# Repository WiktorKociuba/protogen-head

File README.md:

# Protogen head
**WIP**
## Hardware
The PCB for this protogen head contains ESP32-S3-Mini and is powered by two USB-C ports/one USB-C port and XT-30 connector. You can connect to it:
- Two serialy connected Waveshare 22101 (or simillar) LED matrixes
- Two WS2812B LED strips
- Two small fans
- One speaker
- One capacitive button <br>

It also has 15 GPIO pins exposed as well as two of each voltage pins. The +5VD net is used to power only LED Matrixes and the +5V powers the rest. ESP32 works on 3V3, so I had to use a LDO to power it. There are also two 74AHCT245PW used to change the logic voltage from 3V3 to 5V, so it can communicate with the peripherals that require 5V. The production files and LCSC BoM can be found in hardware/protogenHead/jlcpcb/production_files . <br>
 <br>
<br>
<br>
<br>

## 3D Model
**TODO**
## Software
**TODO**

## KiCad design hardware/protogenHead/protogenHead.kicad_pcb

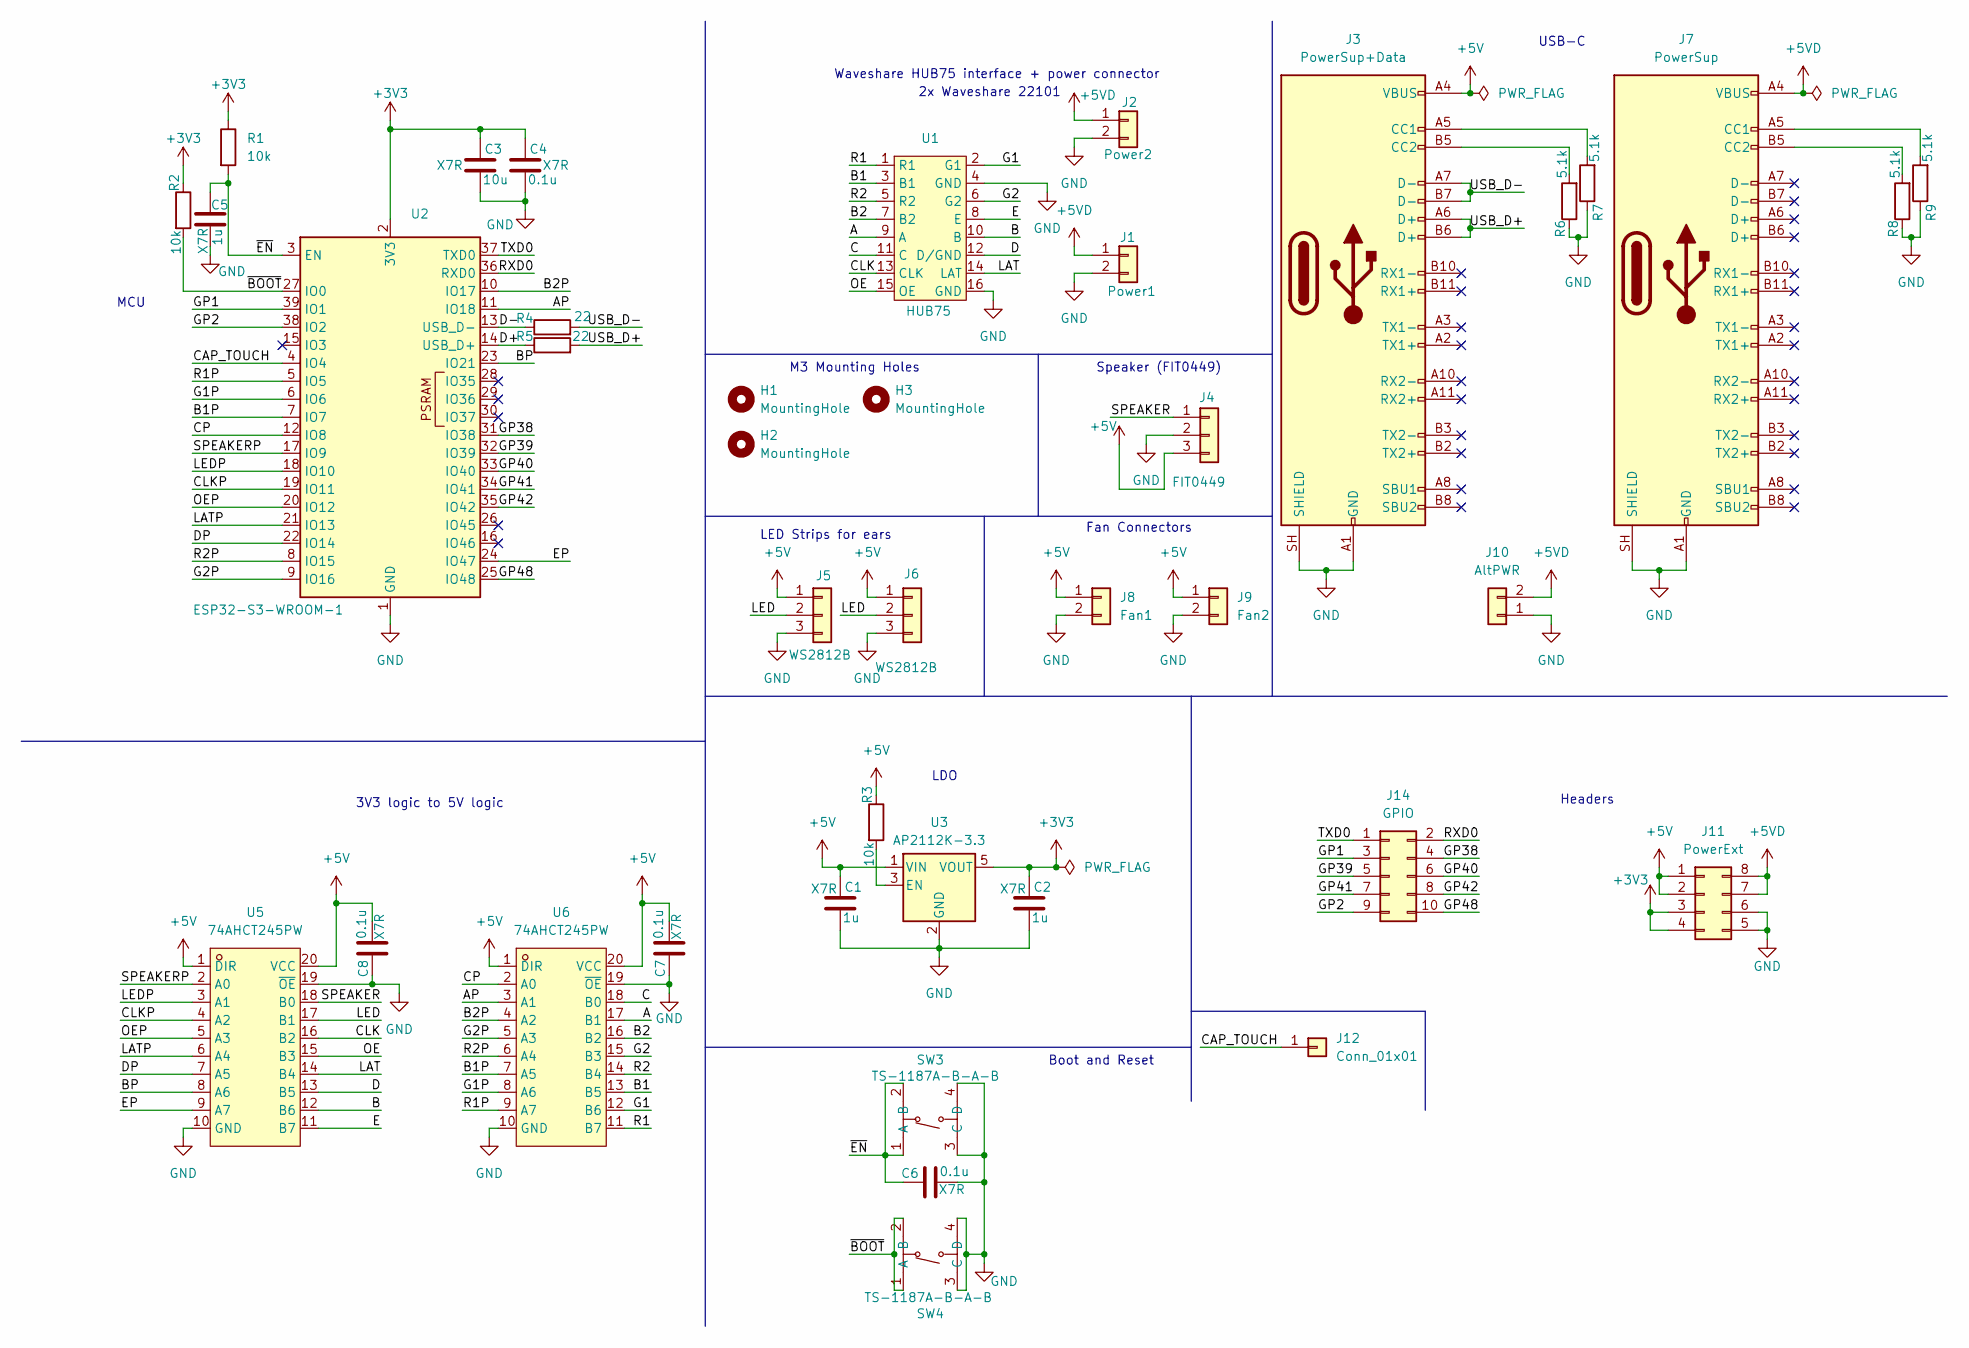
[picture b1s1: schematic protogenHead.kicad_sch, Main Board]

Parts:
C1, C2, C5: 1u; C_0603_1608Metric
C3: 10u; C_0603_1608Metric
C4, C6, C7, C8: 0.1u; C_0603_1608Metric
H1, H2, H3: MountingHole; MountingHole_3.2mm_M3
J1: Power1; TerminalBlock_MaiXu_MX126-5.0-02P_1x02_P5.00mm
J2: Power2; TerminalBlock_MaiXu_MX126-5.0-02P_1x02_P5.00mm
J3: PowerSup+Data; USB_C_Receptacle_HRO_TYPE-C-31-M-12
J4: FIT0449; JST_EH_B3B-EH-A_1x03_P2.50mm_Vertical
J5, J6: WS2812B; JST_EH_B3B-EH-A_1x03_P2.50mm_Vertical
J7: PowerSup; USB_C_Receptacle_HRO_TYPE-C-31-M-12
J8: Fan1; JST_EH_B2B-EH-A_1x02_P2.50mm_Vertical
J9: Fan2; JST_EH_B2B-EH-A_1x02_P2.50mm_Vertical
J10: AltPWR; AMASS_XT30U-F_1x02_P5.0mm_Vertical
J11: PowerExt; PinHeader_2x04_P2.54mm_Vertical
J12: Conn_01x01; PinSocket_1x01_P2.54mm_Vertical
J14: GPIO; PinHeader_2x05_P2.54mm_Vertical
R1, R2, R3: 10k; R_0603_1608Metric
R4, R5: 22; R_0603_1608Metric
R6, R7, R8, R9: 5.1k; R_0603_1608Metric
SW3, SW4: TS-1187A-B-A-B; SW-SMD_4P-L5.1-W5.1-P3.70-LS6.5-TL_H1.5; MPN TS-1187A-B-A-B; LCSC Part C318884
U1: HUB75; IDC-Header_2x08_P2.54mm_Vertical
U2: ESP32-S3-WROOM-1
U3: AP2112K-3.3; SOT-23-5
U5, U6: 74AHCT245PW; TSSOP-20_L6.5-W4.4-P0.65-LS6.4-BL; MPN 74AHCT245PW; LCSC Part C54815895

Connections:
+3V3: C2.1, C3.1, C4.1, J11.3, J11.4, R1.1, R2.1, U2.2 (3V3), U3.5 (VOUT)
+5V: C1.1, C7.2, C8.2, J3.A4 (VBUS), J3.A9 (VBUS), J3.B4 (VBUS), J3.B9 (VBUS), J4.3, J5.1, J6.1, J8.1, J9.1, J11.1, J11.2, R3.1, U3.1 (VIN), U5.1 (DIR), U5.20 (VCC), U6.1 (DIR), U6.20 (VCC)
+5VD: J1.1, J2.1, J7.A4 (VBUS), J7.A9 (VBUS), J7.B4 (VBUS), J7.B9 (VBUS), J10.2, J11.7, J11.8
/A: U1.9 (A), U6.17 (B1)
/AP: U2.11 (IO18), U6.3 (A1)
/B: U1.10 (B), U5.12 (B6)
/B1: U1.3 (B1), U6.13 (B5)
/B1P: U2.7 (IO7), U6.7 (A5)
/B2: U1.7 (B2), U6.16 (B2)
/B2P: U2.10 (IO17), U6.4 (A2)
/BP: U2.23 (IO21), U5.8 (A6)
/C: U1.11 (C), U6.18 (B0)
/CAP_TOUCH: J12.1 (Pin_1_1), U2.4 (IO4)
/CLK: U1.13 (CLK), U5.16 (B2)
/CLKP: U2.19 (IO11), U5.4 (A2)
/CP: U2.12 (IO8), U6.2 (A0)
/D: U1.12 (D/GND), U5.13 (B5)
/D+: R5.1, U2.14 (USB_D+)
/D-: R4.1, U2.13 (USB_D-)
/DP: U2.22 (IO14), U5.7 (A5)
/E: U1.8 (E), U5.11 (B7)
/EP: U2.24 (IO47), U5.9 (A7)
/G1: U1.2 (G1), U6.12 (B6)
/G1P: U2.6 (IO6), U6.8 (A6)
/G2: U1.6 (G2), U6.15 (B3)
/G2P: U2.9 (IO16), U6.5 (A3)
/GP1: J14.3, U2.39 (IO1)
/GP2: J14.9, U2.38 (IO2)
/GP38: J14.4, U2.31 (IO38)
/GP39: J14.5, U2.32 (IO39)
/GP40: J14.6, U2.33 (IO40)
/GP41: J14.7, U2.34 (IO41)
/GP42: J14.8, U2.35 (IO42)
/GP48: J14.10, U2.25 (IO48)
/LAT: U1.14 (LAT), U5.14 (B4)
/LATP: U2.21 (IO13), U5.6 (A4)
/LED: J5.2, J6.2, U5.17 (B1)
/LEDP: U2.18 (IO10), U5.3 (A1)
/OE: U1.15 (OE), U5.15 (B3)
/OEP: U2.20 (IO12), U5.5 (A3)
/R1: U1.1 (R1), U6.11 (B7)
/R1P: U2.5 (IO5), U6.9 (A7)
/R2: U1.5 (R2), U6.14 (B4)
/R2P: U2.8 (IO15), U6.6 (A4)
/RXD0: J14.2, U2.36 (RXD0)
/SPEAKER: J4.1, U5.18 (B0)
/SPEAKERP: U2.17 (IO9), U5.2 (A0)
/TXD0: J14.1, U2.37 (TXD0)
/USB_D+: J3.A6 (D+), J3.B6 (D+), R5.2
/USB_D-: J3.A7 (D-), J3.B7 (D-), R4.2
/~BOOT: R2.2, SW4.1 (A), SW4.2 (B), U2.27 (IO0)
/~EN: C5.1, C6.1, R1.2, SW3.1 (A), SW3.2 (B), U2.3 (EN)
GND: C1.2, C2.2, C3.2, C4.2, C5.2, C6.2, C7.1, C8.1, J1.2, J2.2, J3.A1 (GND), J3.A12 (GND), J3.B1 (GND), J3.B12 (GND), J3.SH (SHIELD), J4.2, J5.3, J6.3, J7.A1 (GND), J7.A12 (GND), J7.B1 (GND), J7.B12 (GND), J7.SH (SHIELD), J8.2, J9.2, J10.1, J11.5, J11.6, R6.1, R7.1, R8.1, R9.1, SW3.3 (C), SW3.4 (D), SW4.3 (C), SW4.4 (D), U1.4 (GND), U1.16 (GND), U2.1 (GND), U2.40 (GND), U2.41 (GND), U3.2 (GND), U5.10 (GND), U5.19 (~OE), U6.10 (GND), U6.19 (~OE)
unnamed: J3.A5 (CC1), R7.2
unnamed: J3.B5 (CC2), R6.2
unnamed: J7.A5 (CC1), R9.2
unnamed: J7.B5 (CC2), R8.2
unnamed: R3.2, U3.3 (EN)

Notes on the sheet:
3V3 logic to 5V logic
Boot and Reset
M3 Mounting Holes
USB-C
Fan Connectors
Speaker (FIT0449)
LDO
Waveshare HUB75 interface + power connector
LED Strips for ears
2x Waveshare 22101
Headers
MCU

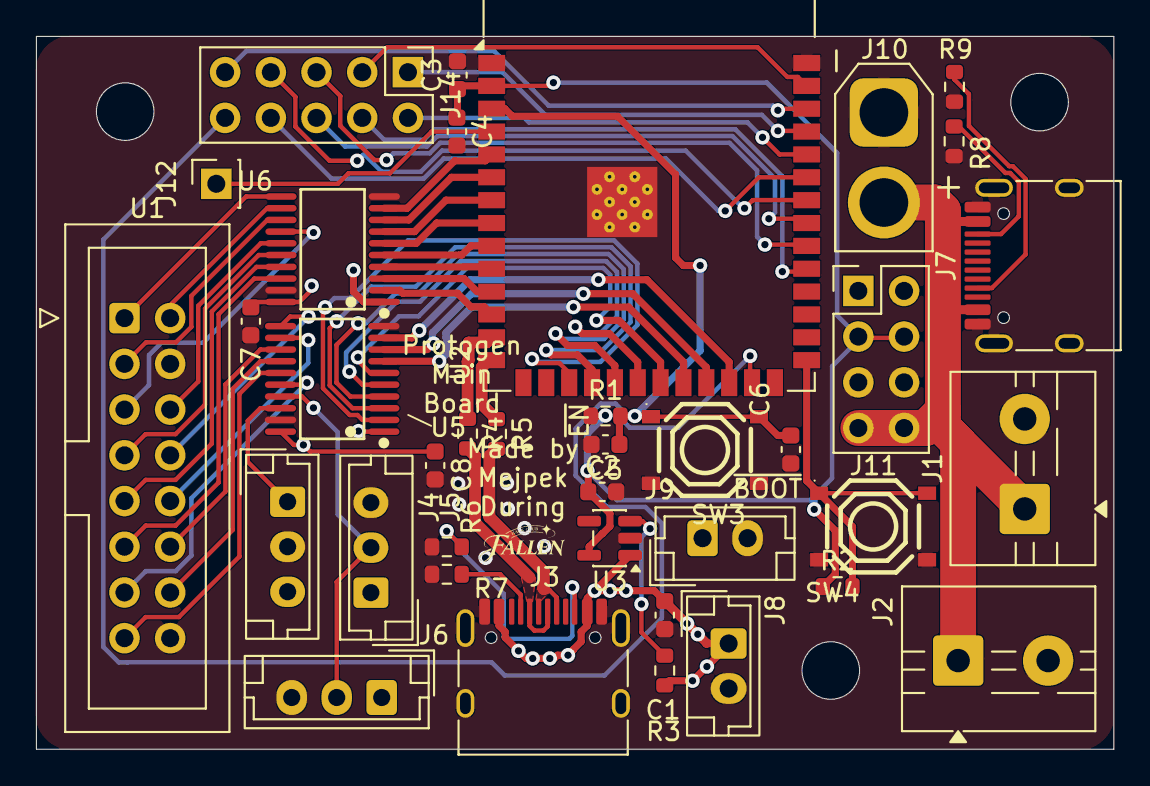
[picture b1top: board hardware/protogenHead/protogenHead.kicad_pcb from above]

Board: 2 copper layers, 59.9 x 39.6 mm, 40 parts (0 on the bottom side), 58 nets.

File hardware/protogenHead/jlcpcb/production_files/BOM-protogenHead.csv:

Comment,Designator,Footprint,LCSC,Quantity
0.1u,"C4,C6,C7,C8",C_0603_1608Metric,C14663,4
10k,"R1,R2,R3",R_0603_1608Metric,C25804,3
10u,C3,C_0603_1608Metric,C19702,1
1u,"C1,C2,C5",C_0603_1608Metric,C15849,3
22,"R4,R5",R_0603_1608Metric,C23345,2
5.1k,"R6,R7,R8,R9",R_0603_1608Metric,C23186,4
74AHCT245PW,"U5,U6",TSSOP-20_L6.5-W4.4-P0.65-LS6.4-BL,C54815895,2
AP2112K-3.3,U3,SOT-23-5,C23380830,1
AltPWR,J10,AMASS_XT30U-F_1x02_P5.0mm_Vertical,C99102,1
Conn_01x01,J12,PinSocket_1x01_P2.54mm_Vertical,C49569624,1
Conn_02x08_Counter_Clockwise,J13,PinHeader_2x08_P2.54mm_Vertical,C5383108,1
ESP32-S3-MINI-1,U4,ESP32-S2-MINI-1,C2913206,1
FIT0449,J4,JST_EH_B3B-EH-A_1x03_P2.50mm_Vertical,C160259,1
Fan1,J8,JST_EH_B2B-EH-A_1x02_P2.50mm_Vertical,C160262,1
Fan2,J9,JST_EH_B2B-EH-A_1x02_P2.50mm_Vertical,C160262,1
HUB75,U1,IDC-Header_2x08_P2.54mm_Vertical,C2884532,1
Power1,J1,TerminalBlock_MaiXu_MX126-5.0-02P_1x02_P5.00mm,C5188434,1
Power2,J2,TerminalBlock_MaiXu_MX126-5.0-02P_1x02_P5.00mm,C5188434,1
PowerExt,J11,PinHeader_2x04_P2.54mm_Vertical,C5383105,1
PowerSup,J7,USB_C_Receptacle_HRO_TYPE-C-31-M-12,C165948,1
PowerSup+Data,J3,USB_C_Receptacle_HRO_TYPE-C-31-M-12,C165948,1
TS-1187A-B-A-B,"SW3,SW4",SW-SMD_4P-L5.1-W5.1-P3.70-LS6.5-TL_H1.5,C318884,2
WS2812B,"J5,J6",JST_EH_B3B-EH-A_1x03_P2.50mm_Vertical,C160259,2

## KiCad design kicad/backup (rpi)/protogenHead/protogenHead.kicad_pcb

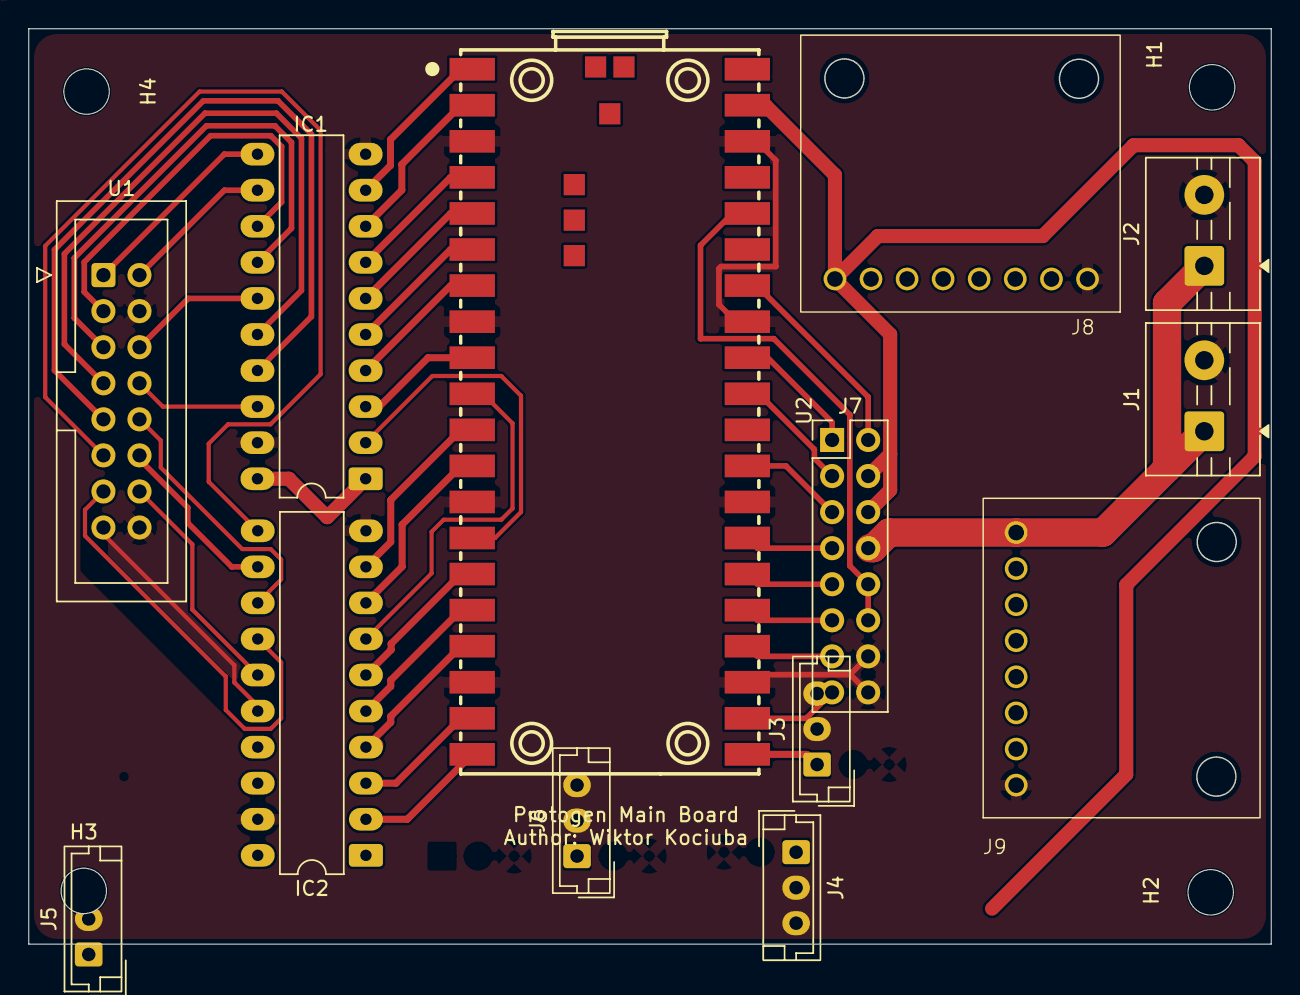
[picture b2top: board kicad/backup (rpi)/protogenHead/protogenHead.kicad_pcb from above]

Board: 2 copper layers, 87.5 x 64.5 mm, 17 parts (0 on the bottom side), 46 nets.

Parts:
H1, H2, H3, H4: MountingHole; MountingHole_3.2mm_M3
IC1, IC2: 74HCT245; DIP-20_W7.62mm_LongPads
J1: Power1; TerminalBlock_MaiXu_MX126-5.0-02P_1x02_P5.00mm
J2: Power2; TerminalBlock_MaiXu_MX126-5.0-02P_1x02_P5.00mm
J3: MotionSensor; JST_EH_B3B-EH-A_1x03_P2.50mm_Vertical
J4: FIT0449; JST_EH_B3B-EH-A_1x03_P2.50mm_Vertical
J5, J6: WS2812B; JST_EH_B3B-EH-A_1x03_P2.50mm_Vertical
J7: GPIO Header; PinHeader_2x08_P2.54mm_Vertical
J8, J9: PiHut 106575; PiHut USB-C
U1: HUB75; IDC-Header_2x08_P2.54mm_Vertical
U2: RASPBERRY PI PICO 2W; Pi Pico 2W

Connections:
+3V3: J3.2, J7.10, J7.12, U2.36 (3V3(OUT))
+5V: IC1.1 (DIR), IC1.20 (VCC), IC2.1 (DIR), IC2.20 (VCC), J4.2, J5.1, J6.1, J7.4, J7.6, J8.A4 (VBUS), U2.39 (VSYS)
+5VD: J1.1, J2.1, J7.8, J9.A4 (VBUS)
/A: IC1.17 (B2), U1.9 (A)
/AP: IC1.3 (A2), U2.9 (GP6_SPI0SCK_I2C1SDA)
/B: IC2.13 (B6), U1.10 (B)
/B1: IC1.13 (B6), U1.3 (B1)
/B1P: IC1.7 (A6), U2.4 (GP2_SPI0SCK_I2C1SDA)
/B2: IC1.16 (B3), U1.7 (B2)
/B2P: IC1.4 (A3), U2.7 (GP5_SPI0CSn_I2C0SCL_UART1RX)
/BP: IC2.7 (A6), U2.10 (GP7_SPI0TX_I2C1SCL)
/C: IC2.11 (B8), U1.11 (C)
/CLK: IC2.14 (B5), U1.13 (CLK)
/CLKP: IC2.6 (A5), U2.15 (GP11_SPI1TX_I2C1SCL)
/CP: IC2.9 (A8), U2.11 (GP8_SPI1RX_I2C0SDA_UART1TX)
/D: IC2.12 (B7), U1.12 (D/GND)
/DP: IC2.8 (A7), U2.12 (GP9_SPI1CSn_I2C0SCL_UART1RX)
/E: IC1.18 (B1), U1.8 (E)
/EP: IC1.2 (A1), U2.14 (GP10_SPI1SCK_I2C1SDA)
/G1: IC1.12 (B7), U1.2 (G1)
/G1P: IC1.8 (A7), U2.2 (GP1_SPI0CSn_I2C0SCL_UART0RX)
/G2: IC1.15 (B4), U1.6 (G2)
/G2P: IC1.5 (A4), U2.6 (GP4_SPI0RX_I2C0SDA_UART1TX)
/GP17: J7.15, U2.22 (GP17_SPI0CSn_UART0TX)
/GP18: J7.13, U2.24 (GP18_SPI0SCK_I2C1SDA)
/GP19: J7.11, U2.25 (GP19_SPI0TX_I2C1SCL)
/GP20: J7.9, U2.26 (GP20_I2C0SDA)
/GP21: J7.7, U2.27 (GP21_I2C0SCL)
/GP22: J7.5, U2.29 (GP22)
/GP26: J7.3, U2.31 (GP26_ADC0_I2C1SDA)
/GP27: J7.1, U2.32 (GP27_ADC1_I2C1SCL)
/GP28: J7.2, U2.34 (GP28_ADC2)
/LAT: IC2.15 (B4), U1.14 (LAT)
/LATP: IC2.5 (A4), U2.16 (GP12_SPI1RX_I2C0SDA_UART0TX)
/LED: IC2.17 (B2), J5.2, J6.2
/LEDP: IC2.3 (A2), U2.19 (GP14_SPI1SCK_I2C1SDA)
/MOTION: J3.1, U2.21 (GP16_SPI0RX_UART0RX)
/OE: IC2.16 (B3), U1.15 (OE)
/OEP: IC2.4 (A3), U2.17 (GP13_SPI1CSn_I2C0SCL_UART0RX)
/R1: IC1.11 (B8), U1.1 (R1)
/R1P: IC1.9 (A8), U2.1 (GP0_SPI0RX_I2C0SDA_UART0TX)
/R2: IC1.14 (B5), U1.5 (R2)
/R2P: IC1.6 (A5), U2.5 (GP3_SPI0TX_I2C1SCL)
/SPEAKER: IC2.18 (B1), J4.1
/SPEAKERP: IC2.2 (A1), U2.20 (GP15_SPI1TX_I2C1SCL)
GND: IC1.10 (GND), IC1.19 (~OE), IC2.10 (GND), IC2.19 (~OE), J1.2, J2.2, J3.3, J4.3, J5.3, J6.3, J7.14, J7.16, J8.A1 (GND), J9.A1 (GND), U1.4 (GND), U1.16 (GND), U2.3 (GND), U2.8 (GND), U2.13 (GND), U2.18 (GND), U2.23 (GND), U2.28 (GND), U2.33 (GND_AGND), U2.38 (GND)
